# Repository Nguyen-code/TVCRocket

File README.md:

# About TVCRocket

This project was simultaneously one of the most challenging and most fun projects I've done in a while. I put myself on an extremely strict deadline, only 6 weeks for everything from planning launch sites to putting together 3 rockets (because I wanted to submit some of the work to colleges for applications) and I'm pleased with the progress I was able to make in that time. Going forward, I'm excited to continue development in future versions.

# Design Intent

The overarching goal of this project was to design and develop an active stability system for rockets on the model scale to learn more about robust hardware, software, and mechanical design. Although the first version didn't exactly work perfectly, I learned __SO MUCH__ and am excited to continue on version two, hopefully in the spring of 2021.

# Pictures!

### Zenith Boards (both controller and flight computer)

### Rockets before launch

### Rocket at launch site in tuning setup

# Renderings

## Zenith

## Controller

# Disclaimer

This repository contains Technical Data whose export is restricted by the Arms Export Control Act (Title 22, U.S.C., Sec 2751, et seq.). It is for educational purposes only and is not meant to be used in any scenarios which would put individuals in danger. When I launched my rocket, I strictly adhered with NAR/Tripoli safety codes. If you use anything from this repository for any means, you release me (Aaron Becker) from all liability and claims.

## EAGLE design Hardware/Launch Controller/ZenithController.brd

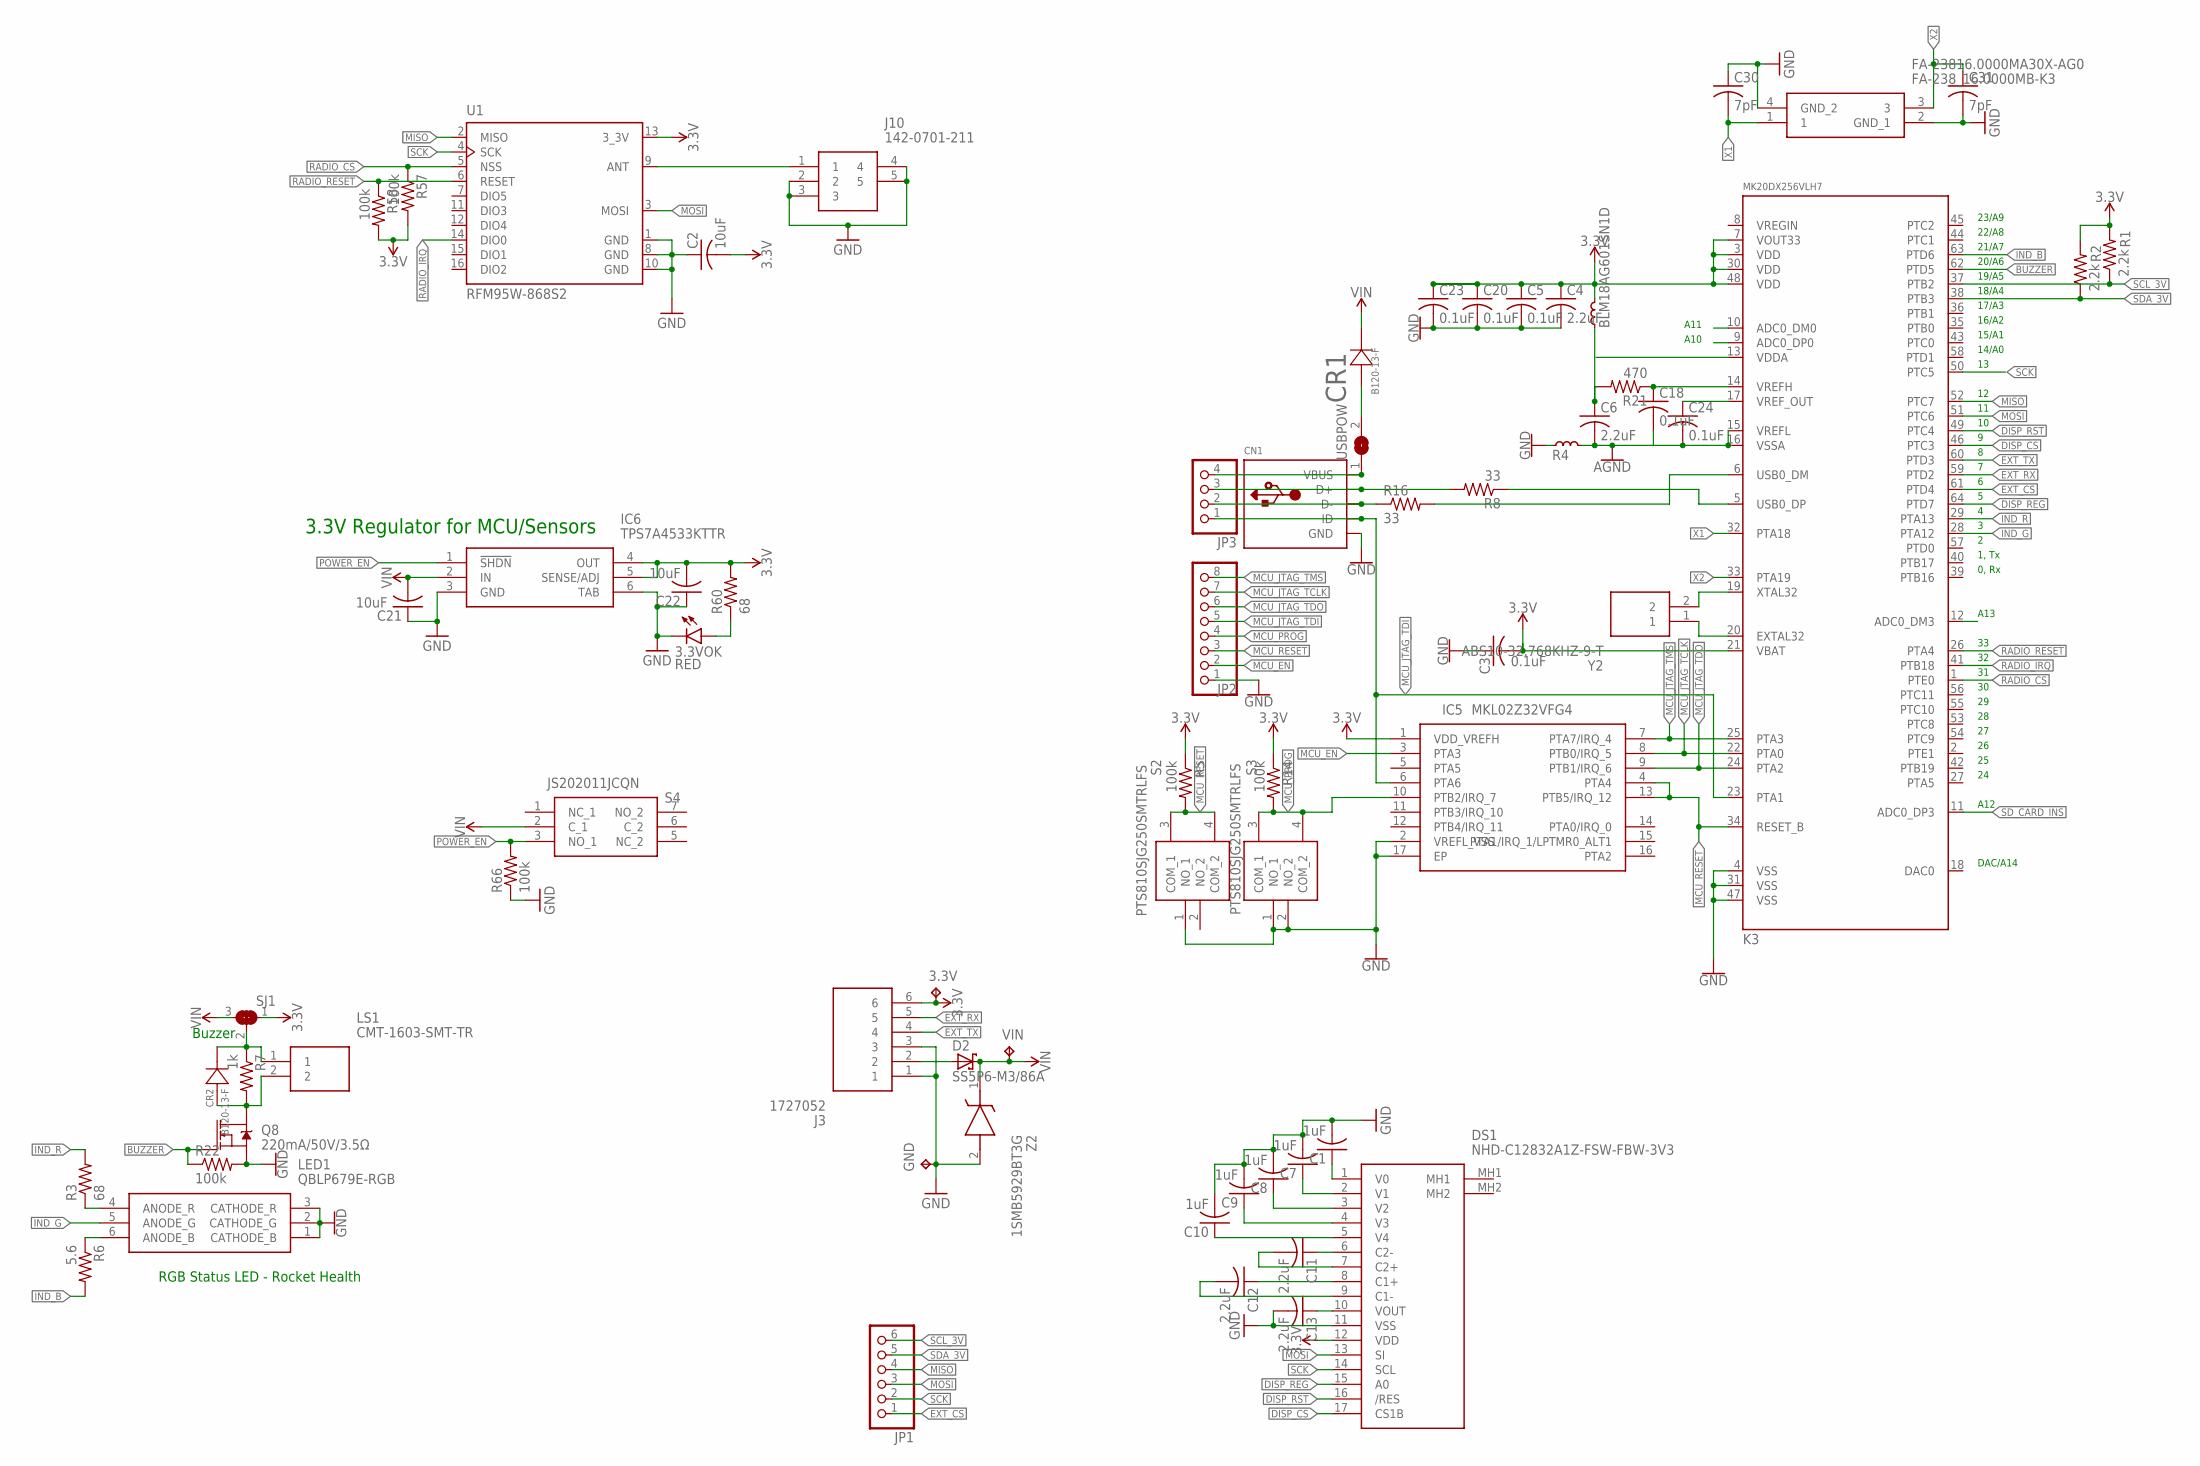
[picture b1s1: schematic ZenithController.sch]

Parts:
3.3V: TPB1,27; B1,27
3.3VOK: RED; CHIP-LED0805
BLM18AG601SN1D: FERRITE; L0603
C1, C7, C8, C9, C10: 1uF; C0603
C2, C21, C22: 10uF; C0603
C3, C5, C18, C20, C23, C24: 0.1uF; C0603
C4, C6, C11, C12, C13: 2.2uF; C0603
C30, C31: 7pF; C0603
CN1: USBMINIB; USB-MINIB
CR1, CR2: B120-13-F; SMA_DIO
D2: SS5P6-M3/86A; TO-277A(SMPC)
DS1: NHD-C12832A1Z-FSW-FBW-3V3; NHDC12832A1ZFSWFBW3V3
FA-23816.0000MA30X-AG0: FA-238_16.0000MB-K3; EPSON-FA-238
GND: TPB1,27; B1,27
IC5: MKL02Z32VFG4; QFN50P300X300X65-17N
IC6: TPS7A4533KTTR; KTT0005B
J3: 1727052; SHDR6W105P0X381_1X6_2285X730X8
J10: 142-0701-211; 1420701211
JP1: PINHD-1X6; 1X06
JP2: PINHD-1X8; 1X08
JP3: PINHD-1X4; 1X04
K3: MK20DX256VLH7; LQFP64-05
LED1: QBLP679E-RGB; QBLP679ERGB
LS1: CMT-1603-SMT-TR; CMT1603SMTTR
Q8: 220mA/50V/3.5Ω; SOT23-3
R1, R2: 2.2k; R0603
R3, R60: 68; R0603
R4: FERRITE; L0603
R5, R14, R22, R57, R58, R66: 100k; R0603
R6: 5.6; R0603
R7: 1k; R0603
R8, R16: 33; R0603
R21: 470; R0603
S2, S3: PTS810SJG250SMTRLFS
S4: JS202011JCQN
SJ1: SOLDERJUMPER_2WAY0603; SOLDERJUMPER_2WAY_OPEN_0603
U1: RFM95W-868S2; XCVR_RFM95W-868S2
USBPOW: SJ
VIN: TPB1,27; B1,27
Y2: ABS10-32.768KHZ-9-T; ABS-10
Z2: 1SMB5929BT3G; DIOM5436X247N

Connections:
3.3V: 3.3V.TP, BLM18AG601SN1D.2, C2.2, C3.2, C4.1, C5.1, C20.1, C22.2, C23.1, DS1.12 (VDD), IC5.1 (VDD_VREFH), IC6.4 (OUT), IC6.5 (SENSE/ADJ), J3.6, K3.3 (VDD), K3.7 (VOUT33), K3.21 (VBAT), K3.30 (VDD), K3.48 (VDD), R1.2, R2.2, R5.1, R14.1, R57.2, R58.2, R60.2, SJ1.1, U1.13 (3_3V)
AGND: C6.2, C18.2, C24.2, K3.15 (VREFL), K3.16 (VSSA), R4.2
BUZZER: K3.62 (PTD5), Q8.1 (G), R22.1
DISP_CS: DS1.17 (CS1B), K3.46 (PTC3)
DISP_REG: DS1.15 (A0), K3.64 (PTD7)
DISP_RST: DS1.16 (/RES), K3.49 (PTC4)
EXT_CS: JP1.1, K3.61 (PTD4)
EXT_RX: J3.5, K3.59 (PTD2)
EXT_TX: J3.4, K3.60 (PTD3)
GND: 3.3VOK.C, C1.2, C2.1, C3.1, C4.2, C5.2, C7.2, C8.2, C9.2, C10.2, C13.2, C20.2, C21.1, C22.1, C23.2, C30.1, C31.2, CN1.GND, DS1.11 (VSS), FA-23816.0000MA30X-AG0.2 (GND_1), FA-23816.0000MA30X-AG0.4 (GND_2), GND.TP, IC5.2 (VREFL_VSS), IC5.17 (EP), IC6.3 (GND), IC6.6 (TAB), J3.1, J3.3, J10.2, J10.3, J10.4, J10.5, JP2.1, K3.4 (VSS), K3.31 (VSS), K3.47 (VSS), LED1.1 (CATHODE_B), LED1.2 (CATHODE_G), LED1.3 (CATHODE_R), Q8.2 (S), R4.1, R22.2, R66.1, S2.1 (NO_1), S3.1 (NO_1), S3.2 (NO_2), U1.1 (GND), U1.8 (GND), U1.10 (GND), Z2.2 (A)
IND_B: K3.63 (PTD6), R6.2
IND_G: K3.28 (PTA12), LED1.5 (ANODE_G)
IND_R: K3.29 (PTA13), R3.2
MCU_EN: IC5.3 (PTA3), JP2.2
MCU_JTAG_TCLK: IC5.8 (PTB0/IRQ_5), JP2.7, K3.22 (PTA0)
MCU_JTAG_TDI: CN1.ID, IC5.6 (PTA6), JP2.5, JP3.1, K3.23 (PTA1)
MCU_JTAG_TDO: IC5.9 (PTB1/IRQ_6), JP2.6, K3.24 (PTA2)
MCU_JTAG_TMS: IC5.7 (PTA7/IRQ_4), JP2.8, K3.25 (PTA3)
MCU_PROG: IC5.10 (PTB2/IRQ_7), JP2.4, R14.2, S3.3 (COM_1), S3.4 (COM_2)
MCU_RESET: IC5.4 (PTA4), IC5.13 (PTB5/IRQ_12), JP2.3, K3.34 (RESET_B), R5.2, S2.3 (COM_1), S2.4 (COM_2)
MISO: JP1.4, K3.52 (PTC7), U1.2 (MISO)
MOSI: DS1.13 (SI), JP1.3, K3.51 (PTC6), U1.3 (MOSI)
unnamed: C1.1, DS1.1 (V0)
unnamed: LED1.4 (ANODE_R), R3.1
unnamed: K3.19 (XTAL32), Y2.2
unnamed: BLM18AG601SN1D.1, C6.1, R21.2
unnamed: C7.1, DS1.2 (V1)
unnamed: LED1.6 (ANODE_B), R6.1
unnamed: CR2.2, LS1.2, Q8.3 (D), R7.2
unnamed: J10.1, U1.9 (ANT)
unnamed: C8.1, DS1.3 (V2)
unnamed: C24.1, K3.17 (VREF_OUT)
unnamed: 3.3VOK.A, R60.1
unnamed: C9.1, DS1.4 (V3)
unnamed: C10.1, DS1.5 (V4)
unnamed: C13.1, DS1.10 (VOUT)
unnamed: C11.1, DS1.6 (C2-)
unnamed: C11.2, DS1.7 (C2+)
unnamed: C12.1, DS1.8 (C1+)
unnamed: C12.2, DS1.9 (C1-)
unnamed: CN1.D+, JP3.3, R8.2
unnamed: CN1.D-, JP3.2, R16.1
unnamed: K3.5 (USB0_DP), R8.1
unnamed: K3.6 (USB0_DM), R16.2
unnamed: CR1.2, USBPOW.2
unnamed: CN1.VBUS, JP3.4, USBPOW.1
unnamed: C18.1, K3.14 (VREFH), R21.1
unnamed: CR2.1, LS1.1, R7.1, SJ1.2
unnamed: D2.A1 (A), D2.A2 (A), J3.2
unnamed: K3.20 (EXTAL32), Y2.1
POWER_EN: IC6.1 (!SHDN), R66.2, S4.3 (NO_1)
RADIO_CS: K3.1 (PTE0), R57.1, U1.5 (NSS)
RADIO_IRQ: K3.41 (PTB18), U1.14 (DIO0)
RADIO_RESET: K3.26 (PTA4), R58.1, U1.6 (RESET)
SCK: DS1.14 (SCL), JP1.2, K3.50 (PTC5), U1.4 (SCK)
SCL_3V: JP1.6, K3.37 (PTB2), R1.1
SDA_3V: JP1.5, K3.38 (PTB3), R2.1
SD_CARD_INS: K3.11 (ADC0_DP3)
VIN: C21.2, CR1.1, D2.K (C), IC6.2 (IN), S4.2 (C_1), SJ1.3, VIN.TP, Z2.1 (K)
X1: C30.2, FA-23816.0000MA30X-AG0.1, K3.32 (PTA18)
X2: C31.1, FA-23816.0000MA30X-AG0.3, K3.33 (PTA19)

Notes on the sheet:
23/A9
22/A8
21/A7
20/A6
19/A5
18/A4
17/A3
16/A2
15/A1
14/A0
1, Tx
0, Rx
A13
A12
DAC/A14
A11
A10
3.3V Regulator for MCU/Sensors
Buzzer
RGB Status LED - Rocket Health

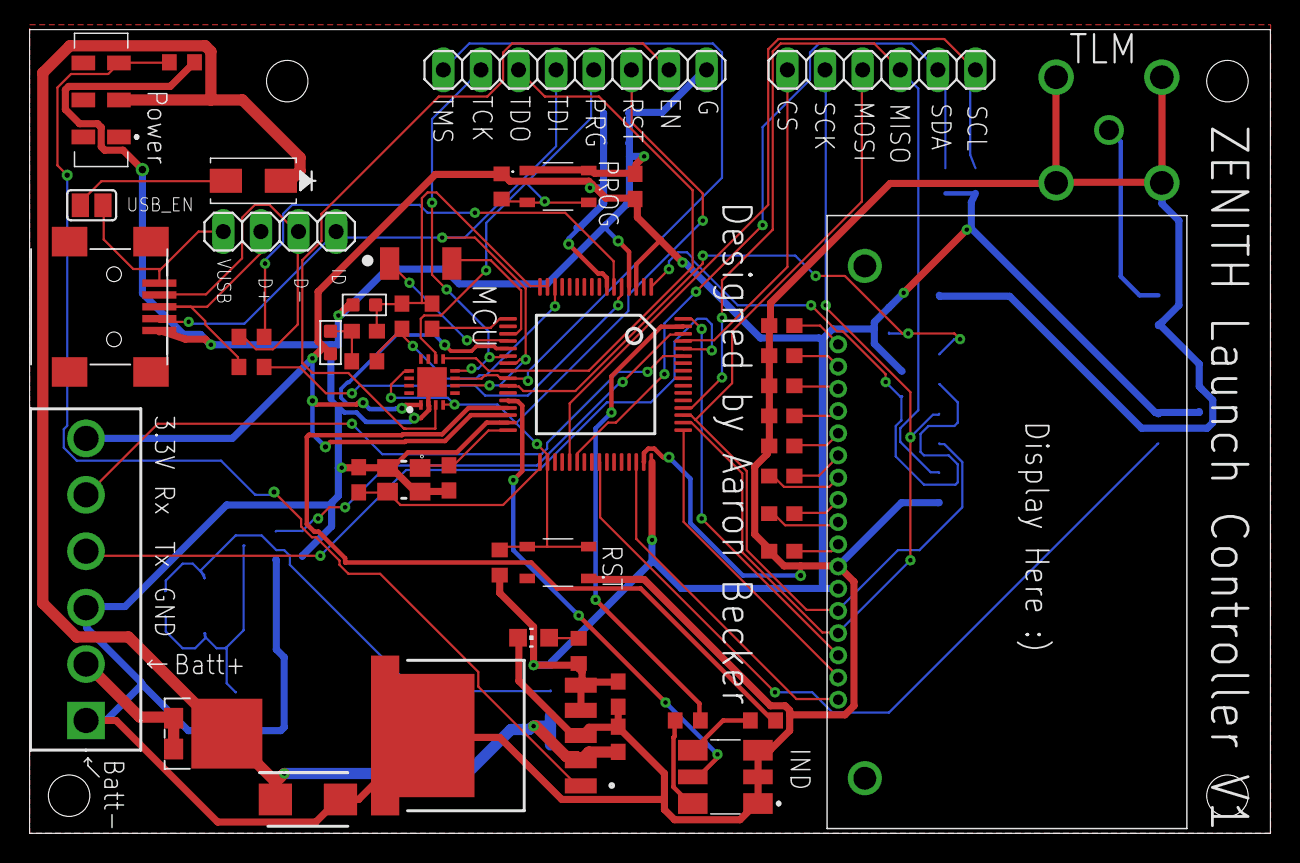
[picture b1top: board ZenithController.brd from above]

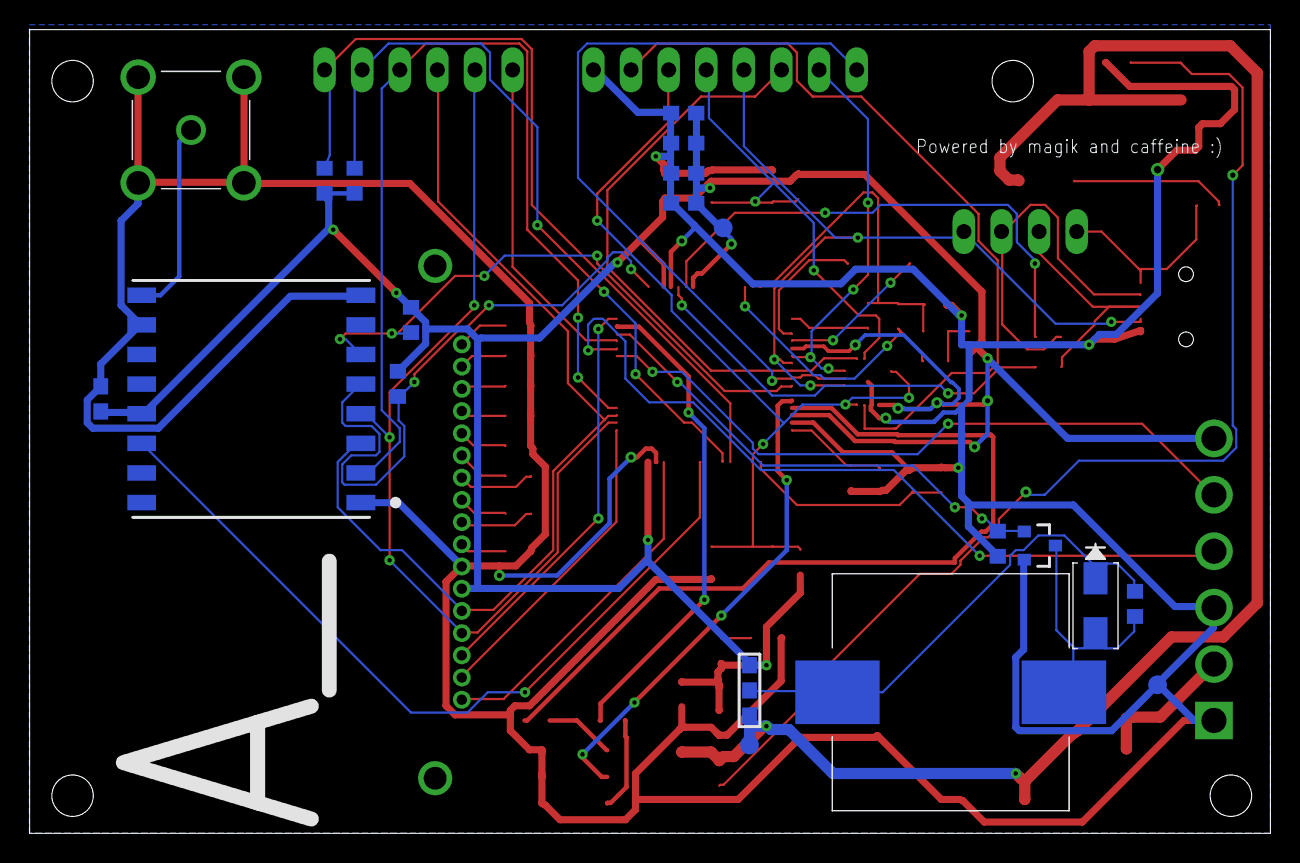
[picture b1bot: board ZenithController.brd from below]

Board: 2 copper layers, 83.8 x 54.3 mm, 67 parts (20 on the bottom side), 60 nets.

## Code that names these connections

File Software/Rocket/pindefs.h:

#ifndef pindefs_h
#define pindefs_h

#include "Arduino.h"

/*
DEVICE I2C ADDRESSES
*/

#define BARO_I2C_ADDR 0x77
#define GYRO_I2C_ADDR 0x68
#define ACC_I2C_ADDR 0x18
#define MAG_I2C_ADDR 0x10
#define GPS_I2C_ADDR 0x42
#define ADC1_I2C_ADDR 0x48
#define ADC2_I2C_ADDR 0x49

/*
INDICATOR PINS
*/

#define IND_R_PIN 4
#define IND_G_PIN 3
#define IND_B_PIN 21

#define BUZZER_PIN 20

/*
PYRO PINS
*/

#define PYRO1_PIN 2
#define PYRO2_PIN 14
#define PYRO3_PIN 15
#define PYRO4_PIN 16
#define PYRO5_PIN 17

/*
TVC PINS
*/

#define TVC_X_CH1_PIN 22
#define TVC_Y_CH1_PIN 23
#define TVC_X_CH2_PIN 5
#define TVC_Y_CH2_PIN 6

/*
ROLL MOTOR PINS
*/
#define ROLL_FIN 9
#define ROLL_RIN 25

/*
SPI PINS
*/

#define SD_CS 10
#define SD_INS A12

#define RADIO_RESET 33
#define RADIO_IRQ 32
#define RADIO_CS 31

#define FLASH_CS 24

#endif

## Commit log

2020-09-25 a lot
2020-09-26 parachute dep
2020-09-26 ready for chute ejection testing
2020-09-26 cleanup
2020-09-28 updated file structure and added progress pictures
2020-10-02 cad part 1
2020-10-07 Create thecodes
2020-10-08 updated ee stuff for the lads on bps discord
2020-10-08 Create LICENSE
2020-10-09 designed test fixture stuff and roll wheel updates
2020-10-10 THECODES
    aka testing scripts
2020-10-10 semi fix
2020-10-11 bonk
2020-10-11 hey tvc
2020-10-11 beginnng tuning!
2020-10-11 WORKING!
2020-10-11 range fix
2020-10-11 more efficient ori calc
2020-10-11 fixed axes inversion and issues
2020-10-15 upload because power might do a die
2020-10-16 lotsa fixes but oop i gotta fly in 2 days
2020-10-17 ready for launch?
2020-10-17 ready for launch
2020-10-20 it went
2020-10-21 final solidworks modelling
2020-10-23 some notes
2020-10-26 markdown and description
2020-10-26 readme fix
2020-10-26 quick reorder
2020-10-26 updated ee stuff
2020-11-02 solidworks sims and references for v2
2020-11-02 reference things more
2020-11-10 more reference
2020-11-22 lots more ideas!
2020-12-24 latest before trip
2021-01-02 additional stuff
2021-01-06 to go with ground station software
2021-01-06 for graphing
2021-01-12 some stuff for most recent updates
2021-03-08 xbeeeee
2021-03-10 xbee stuff
2021-03-11 aes works!
2021-03-11 encryptPacket function done
2021-03-11 lessened memory needs for AES encryption
2021-03-11 First working AES sending!
    AESEncryptTime: 0.148ms, XBeeSendTime: 8.089ms
    FULLS_STATE: 8.237ms
    AESEncryptTime: 0.179ms, XBeeSendTime: 9.561ms
    FULLS_SENSOR: 9.740ms
2021-03-12 aes and packet type stuff is done, it works!
2021-03-13 i2c tester stuff works
2021-03-13 dual band tests
2021-03-24 joe's telem
2021-04-19 fsf stuff
2021-07-27 jb final changes

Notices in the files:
parts and their libraries:
SparkFun-DiscreteSemi: Licensing: Creative Commons ShareAlike 4.0 International - https://creativecommons.org/licenses/by-sa/4.0
microbuilder: This work is placed in the public domain, and may be freely used for commercial and non-commercial work with the following conditions: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
